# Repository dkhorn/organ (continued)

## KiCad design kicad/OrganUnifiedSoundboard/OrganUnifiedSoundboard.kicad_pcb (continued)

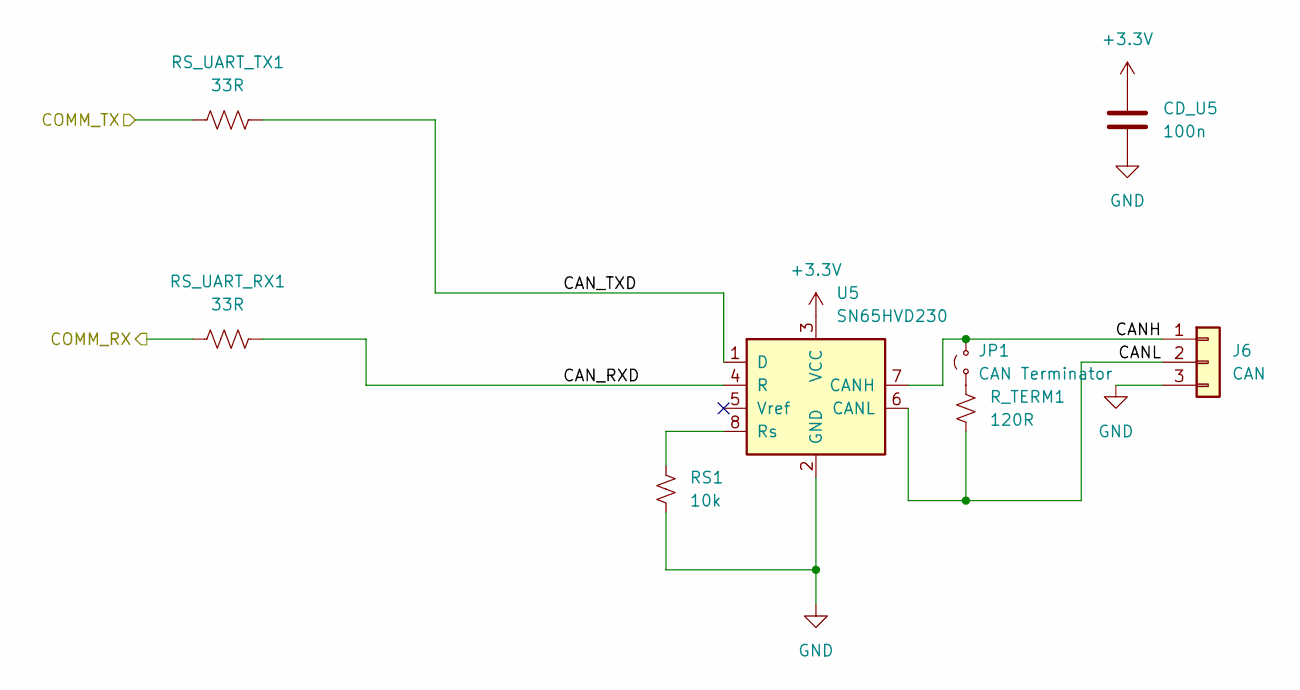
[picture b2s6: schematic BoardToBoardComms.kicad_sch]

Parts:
CD_U5: 100n; C_0603_1608Metric
J6: CAN; JST_PH_B3B-PH-K_1x03_P2.00mm_Vertical
JP1: CAN Terminator; PinHeader_1x02_P2.54mm_Vertical
RS1: 10k; R_0603_1608Metric
RS_UART_RX1: 33R; R_0603_1608Metric
RS_UART_TX1: 33R; R_0603_1608Metric
R_TERM1: 120R; R_0603_1608Metric
U5: SN65HVD230; SOIC-8_3.9x4.9mm_P1.27mm

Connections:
+3.3V: CD_U5.1, U5.3 (VCC); also elsewhere on the board
/Controller/BoardToBoardComms/CANH: J6.1, JP1.2 (B), U5.7 (CANH); also elsewhere on the board
/Controller/BoardToBoardComms/CANL: J6.2, R_TERM1.2, U5.6 (CANL); also elsewhere on the board
/Controller/BoardToBoardComms/CAN_RXD: RS_UART_RX1.2, U5.4 (R)
/Controller/BoardToBoardComms/CAN_TXD: RS_UART_TX1.2, U5.1 (D)
/Controller/COMM_RX: RS_UART_RX1.1; also elsewhere on the board
/Controller/COMM_TX: RS_UART_TX1.1; also elsewhere on the board
GND: CD_U5.2, J6.3, RS1.2, U5.2 (GND); also elsewhere on the board
unnamed: JP1.1 (A), R_TERM1.1
unnamed: RS1.1, U5.8 (Rs)

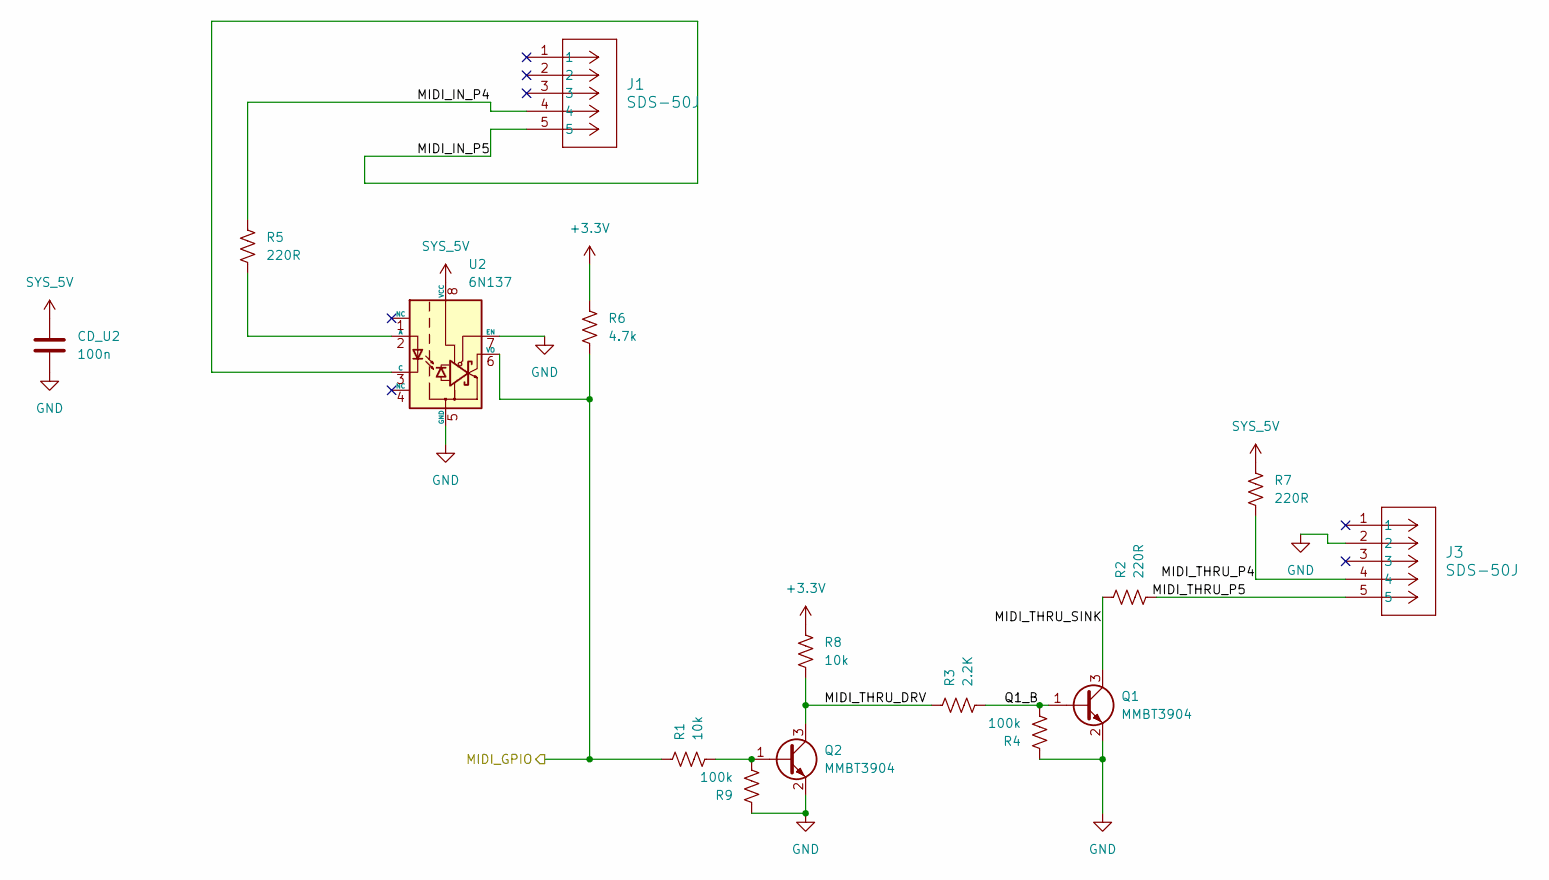
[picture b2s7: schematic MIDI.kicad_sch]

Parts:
CD_U2: 100n; C_0603_1608Metric
J1, J3: SDS-50J; CONN5_SDS-50J_CUD
Q1, Q2: MMBT3904; SOT-23
R1, R8: 10k; R_0603_1608Metric
R2, R5, R7: 220R; R_0603_1608Metric
R3: 2.2K; R_0603_1608Metric
R4, R9: 100k; R_0603_1608Metric
R6: 4.7k; R_0603_1608Metric
U2: 6N137; DIP-8_W7.62mm

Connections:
+3.3V: R6.1, R8.1; also elsewhere on the board
/Controller/MIDI/MIDI_IN_P4: J1.4, R5.1
/Controller/MIDI/MIDI_IN_P5: J1.5, U2.3 (C)
/Controller/MIDI/MIDI_THRU_DRV: Q2.3 (C), R3.1, R8.2
/Controller/MIDI/MIDI_THRU_P4: J3.4, R7.2
/Controller/MIDI/MIDI_THRU_P5: J3.5, R2.2
/Controller/MIDI/MIDI_THRU_SINK: Q1.3 (C), R2.1
/Controller/MIDI/Q1_B: Q1.1 (B), R3.2, R4.2
/Controller/MIDI_GPIO: R1.1, R6.2, U2.6 (VO); also elsewhere on the board
GND: CD_U2.2, J3.2, Q1.2 (E), Q2.2 (E), R4.1, R9.1, U2.5 (GND), U2.7 (EN); also elsewhere on the board
unnamed: Q2.1 (B), R1.2, R9.2
unnamed: R5.2, U2.2 (A)
SYS_5V: CD_U2.1, R7.1, U2.8 (VCC); also elsewhere on the board

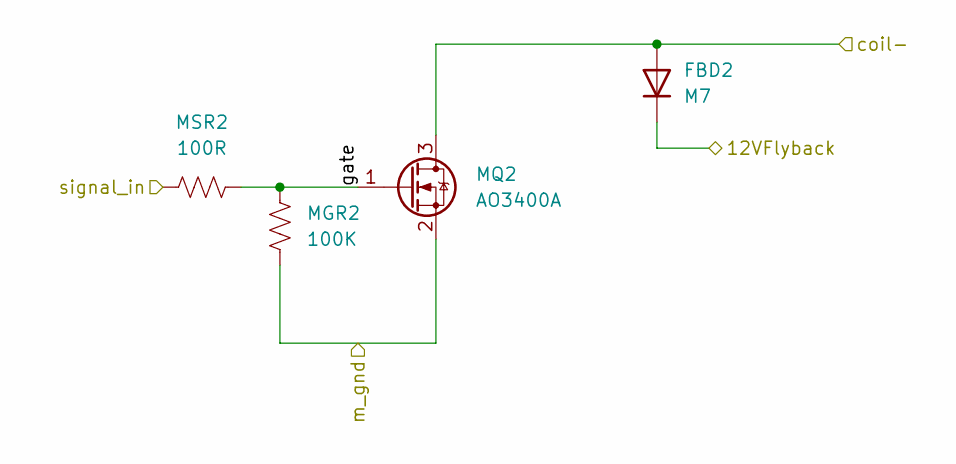
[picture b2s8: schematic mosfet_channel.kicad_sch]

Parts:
FBD2: M7; D_SMA
MGR2: 100K; R_0603_1608Metric
MQ2: AO3400A; SOT-23
MSR2: 100R; R_0603_1608Metric

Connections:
+12V: FBD2.1 (K); also elsewhere on the board
/outputs/16_channel_output_block/16_channel_mosfet_output/mosfet_channel1/gate: MGR2.1, MQ2.1 (G), MSR2.2
/outputs/16_channel_output_block/GND_COIL: MGR2.2, MQ2.2 (S); also elsewhere on the board
/outputs/16_channel_output_block/N01: MSR2.1; also elsewhere on the board
/outputs/coil_o1: FBD2.2 (A), MQ2.3 (D); also elsewhere on the board

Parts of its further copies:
FBD1, FBD3, FBD4, FBD5, FBD6, FBD7, FBD8, FBD9, FBD10, FBD11, FBD12, FBD13, FBD14, FBD15, FBD16, FBD17, FBD18, FBD19, FBD20, FBD21, FBD22, FBD23, FBD24, FBD25, FBD26, FBD27, FBD28, FBD29, FBD30, FBD31, FBD32, FBD33, FBD34, FBD35, FBD36, FBD37, FBD38, FBD39, FBD40, FBD41, FBD42, FBD43, FBD44, FBD45, FBD46, FBD47, FBD48, FBD49, FBD50, FBD51, FBD52, FBD53, FBD54, FBD55, FBD56, FBD57, FBD58, FBD59, FBD60, FBD61, FBD62, FBD63, FBD64, FBD65, FBD66, FBD67, FBD68, FBD69, FBD70, FBD71, FBD72, FBD73, FBD74, FBD75, FBD76, FBD77, FBD78, FBD79, FBD80: M7; D_SMA
MGR1, MGR3, MGR4, MGR5, MGR6, MGR7, MGR8, MGR9, MGR10, MGR11, MGR12, MGR13, MGR14, MGR15, MGR16, MGR17, MGR18, MGR19, MGR20, MGR21, MGR22, MGR23, MGR24, MGR25, MGR26, MGR27, MGR28, MGR29, MGR30, MGR31, MGR32, MGR33, MGR34, MGR35, MGR36, MGR37, MGR38, MGR39, MGR40, MGR41, MGR42, MGR43, MGR44, MGR45, MGR46, MGR47, MGR48, MGR49, MGR50, MGR51, MGR52, MGR53, MGR54, MGR55, MGR56, MGR57, MGR58, MGR59, MGR60, MGR61, MGR62, MGR63, MGR64, MGR65, MGR66, MGR67, MGR68, MGR69, MGR70, MGR71, MGR72, MGR73, MGR74, MGR75, MGR76, MGR77, MGR78, MGR79, MGR80: 100K; R_0603_1608Metric
MQ1, MQ3, MQ4, MQ5, MQ6, MQ7, MQ8, MQ9, MQ10, MQ11, MQ12, MQ13, MQ14, MQ15, MQ16, MQ17, MQ18, MQ19, MQ20, MQ21, MQ22, MQ23, MQ24, MQ25, MQ26, MQ27, MQ28, MQ29, MQ30, MQ31, MQ32, MQ33, MQ34, MQ35, MQ36, MQ37, MQ38, MQ39, MQ40, MQ41, MQ42, MQ43, MQ44, MQ45, MQ46, MQ47, MQ48, MQ49, MQ50, MQ51, MQ52, MQ53, MQ54, MQ55, MQ56, MQ57, MQ58, MQ59, MQ60, MQ61, MQ62, MQ63, MQ64, MQ65, MQ66, MQ67, MQ68, MQ69, MQ70, MQ71, MQ72, MQ73, MQ74, MQ75, MQ76, MQ77, MQ78, MQ79, MQ80: AO3400A; SOT-23
MSR1, MSR3, MSR4, MSR5, MSR6, MSR7, MSR8, MSR9, MSR10, MSR11, MSR12, MSR13, MSR14, MSR15, MSR16, MSR17, MSR18, MSR19, MSR20, MSR21, MSR22, MSR23, MSR24, MSR25, MSR26, MSR27, MSR28, MSR29, MSR30, MSR31, MSR32, MSR33, MSR34, MSR35, MSR36, MSR37, MSR38, MSR39, MSR40, MSR41, MSR42, MSR43, MSR44, MSR45, MSR46, MSR47, MSR48, MSR49, MSR50, MSR51, MSR52, MSR53, MSR54, MSR55, MSR56, MSR57, MSR58, MSR59, MSR60, MSR61, MSR62, MSR63, MSR64, MSR65, MSR66, MSR67, MSR68, MSR69, MSR70, MSR71, MSR72, MSR73, MSR74, MSR75, MSR76, MSR77, MSR78, MSR79, MSR80: 100R; R_0603_1608Metric

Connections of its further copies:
+12V: FBD1.1 (K), FBD3.1 (K), FBD4.1 (K), FBD5.1 (K), FBD6.1 (K), FBD7.1 (K), FBD8.1 (K), FBD9.1 (K), FBD10.1 (K), FBD11.1 (K), FBD12.1 (K), FBD13.1 (K), FBD14.1 (K), FBD15.1 (K), FBD16.1 (K), FBD17.1 (K), FBD18.1 (K), FBD19.1 (K), FBD20.1 (K), FBD21.1 (K), FBD22.1 (K), FBD23.1 (K), FBD24.1 (K), FBD25.1 (K), FBD26.1 (K), FBD27.1 (K), FBD28.1 (K), FBD29.1 (K), FBD30.1 (K), FBD31.1 (K), FBD32.1 (K), FBD33.1 (K), FBD34.1 (K), FBD35.1 (K), FBD36.1 (K), FBD37.1 (K), FBD38.1 (K), FBD39.1 (K), FBD40.1 (K), FBD41.1 (K), FBD42.1 (K), FBD43.1 (K), FBD44.1 (K), FBD45.1 (K), FBD46.1 (K), FBD47.1 (K), FBD48.1 (K), FBD49.1 (K), FBD50.1 (K), FBD51.1 (K), FBD52.1 (K), FBD53.1 (K), FBD54.1 (K), FBD55.1 (K), FBD56.1 (K), FBD57.1 (K), FBD58.1 (K), FBD59.1 (K), FBD60.1 (K), FBD61.1 (K), FBD62.1 (K), FBD63.1 (K), FBD64.1 (K), FBD65.1 (K), FBD66.1 (K), FBD67.1 (K), FBD68.1 (K), FBD69.1 (K), FBD70.1 (K), FBD71.1 (K), FBD72.1 (K), FBD73.1 (K), FBD74.1 (K), FBD75.1 (K), FBD76.1 (K), FBD77.1 (K), FBD78.1 (K), FBD79.1 (K), FBD80.1 (K); also elsewhere on the board
/outputs/16_channel_output_block1/16_channel_mosfet_output/mosfet_channel1/gate: MGR17.1, MQ17.1 (G), MSR17.2
/outputs/16_channel_output_block1/16_channel_mosfet_output/mosfet_channel2/gate: MGR18.1, MQ18.1 (G), MSR18.2
/outputs/16_channel_output_block1/16_channel_mosfet_output/mosfet_channel3/gate: MGR20.1, MQ20.1 (G), MSR20.2
/outputs/16_channel_output_block1/16_channel_mosfet_output/mosfet_channel4/gate: MGR19.1, MQ19.1 (G), MSR19.2
/outputs/16_channel_output_block1/16_channel_mosfet_output/mosfet_channel5/gate: MGR29.1, MQ29.1 (G), MSR29.2
/outputs/16_channel_output_block1/16_channel_mosfet_output/mosfet_channel6/gate: MGR30.1, MQ30.1 (G), MSR30.2
/outputs/16_channel_output_block1/16_channel_mosfet_output/mosfet_channel7/gate: MGR31.1, MQ31.1 (G), MSR31.2
/outputs/16_channel_output_block1/16_channel_mosfet_output/mosfet_channel8/gate: MGR32.1, MQ32.1 (G), MSR32.2
/outputs/16_channel_output_block1/16_channel_mosfet_output/mosfet_channel9/gate: MGR22.1, MQ22.1 (G), MSR22.2
/outputs/16_channel_output_block1/16_channel_mosfet_output/mosfet_channel10/gate: MGR21.1, MQ21.1 (G), MSR21.2
/outputs/16_channel_output_block1/16_channel_mosfet_output/mosfet_channel11/gate: MGR23.1, MQ23.1 (G), MSR23.2
/outputs/16_channel_output_block1/16_channel_mosfet_output/mosfet_channel12/gate: MGR24.1, MQ24.1 (G), MSR24.2
/outputs/16_channel_output_block1/16_channel_mosfet_output/mosfet_channel13/gate: MGR27.1, MQ27.1 (G), MSR27.2
/outputs/16_channel_output_block1/16_channel_mosfet_output/mosfet_channel14/gate: MGR26.1, MQ26.1 (G), MSR26.2
/outputs/16_channel_output_block1/16_channel_mosfet_output/mosfet_channel15/gate: MGR28.1, MQ28.1 (G), MSR28.2
/outputs/16_channel_output_block1/16_channel_mosfet_output/mosfet_channel16/gate: MGR25.1, MQ25.1 (G), MSR25.2
/outputs/16_channel_output_block1/GND_COIL: MGR17.2, MGR18.2, MGR19.2, MGR20.2, MGR21.2, MGR22.2, MGR23.2, MGR24.2, MGR25.2, MGR26.2, MGR27.2, MGR28.2, MGR29.2, MGR30.2, MGR31.2, MGR32.2, MQ17.2 (S), MQ18.2 (S), MQ19.2 (S), MQ20.2 (S), MQ21.2 (S), MQ22.2 (S), MQ23.2 (S), MQ24.2 (S), MQ25.2 (S), MQ26.2 (S), MQ27.2 (S), MQ28.2 (S), MQ29.2 (S), MQ30.2 (S), MQ31.2 (S), MQ32.2 (S); also elsewhere on the board
/outputs/16_channel_output_block1/N01: MSR17.1; also elsewhere on the board
/outputs/16_channel_output_block1/N02: MSR18.1; also elsewhere on the board
/outputs/16_channel_output_block1/N03: MSR20.1; also elsewhere on the board
/outputs/16_channel_output_block1/N04: MSR19.1; also elsewhere on the board
/outputs/16_channel_output_block1/N05: MSR29.1; also elsewhere on the board
/outputs/16_channel_output_block1/N06: MSR30.1; also elsewhere on the board
/outputs/16_channel_output_block1/N07: MSR31.1; also elsewhere on the board
/outputs/16_channel_output_block1/N08: MSR32.1; also elsewhere on the board
/outputs/16_channel_output_block1/N09: MSR22.1; also elsewhere on the board
/outputs/16_channel_output_block1/N10: MSR21.1; also elsewhere on the board
/outputs/16_channel_output_block1/N11: MSR23.1; also elsewhere on the board
/outputs/16_channel_output_block1/N12: MSR24.1; also elsewhere on the board
/outputs/16_channel_output_block1/N13: MSR27.1; also elsewhere on the board
/outputs/16_channel_output_block1/N14: MSR26.1; also elsewhere on the board
/outputs/16_channel_output_block1/N15: MSR28.1; also elsewhere on the board
/outputs/16_channel_output_block1/N16: MSR25.1; also elsewhere on the board
/outputs/16_channel_output_block2/16_channel_mosfet_output/mosfet_channel1/gate: MGR33.1, MQ33.1 (G), MSR33.2
/outputs/16_channel_output_block2/16_channel_mosfet_output/mosfet_channel2/gate: MGR34.1, MQ34.1 (G), MSR34.2
/outputs/16_channel_output_block2/16_channel_mosfet_output/mosfet_channel3/gate: MGR36.1, MQ36.1 (G), MSR36.2
/outputs/16_channel_output_block2/16_channel_mosfet_output/mosfet_channel4/gate: MGR35.1, MQ35.1 (G), MSR35.2
/outputs/16_channel_output_block2/16_channel_mosfet_output/mosfet_channel5/gate: MGR45.1, MQ45.1 (G), MSR45.2
/outputs/16_channel_output_block2/16_channel_mosfet_output/mosfet_channel6/gate: MGR46.1, MQ46.1 (G), MSR46.2
/outputs/16_channel_output_block2/16_channel_mosfet_output/mosfet_channel7/gate: MGR47.1, MQ47.1 (G), MSR47.2
/outputs/16_channel_output_block2/16_channel_mosfet_output/mosfet_channel8/gate: MGR48.1, MQ48.1 (G), MSR48.2
/outputs/16_channel_output_block2/16_channel_mosfet_output/mosfet_channel9/gate: MGR38.1, MQ38.1 (G), MSR38.2
/outputs/16_channel_output_block2/16_channel_mosfet_output/mosfet_channel10/gate: MGR37.1, MQ37.1 (G), MSR37.2
/outputs/16_channel_output_block2/16_channel_mosfet_output/mosfet_channel11/gate: MGR39.1, MQ39.1 (G), MSR39.2
/outputs/16_channel_output_block2/16_channel_mosfet_output/mosfet_channel12/gate: MGR40.1, MQ40.1 (G), MSR40.2
/outputs/16_channel_output_block2/16_channel_mosfet_output/mosfet_channel13/gate: MGR43.1, MQ43.1 (G), MSR43.2
/outputs/16_channel_output_block2/16_channel_mosfet_output/mosfet_channel14/gate: MGR42.1, MQ42.1 (G), MSR42.2
/outputs/16_channel_output_block2/16_channel_mosfet_output/mosfet_channel15/gate: MGR44.1, MQ44.1 (G), MSR44.2
/outputs/16_channel_output_block2/16_channel_mosfet_output/mosfet_channel16/gate: MGR41.1, MQ41.1 (G), MSR41.2
/outputs/16_channel_output_block2/GND_COIL: MGR33.2, MGR34.2, MGR35.2, MGR36.2, MGR37.2, MGR38.2, MGR39.2, MGR40.2, MGR41.2, MGR42.2, MGR43.2, MGR44.2, MGR45.2, MGR46.2, MGR47.2, MGR48.2, MQ33.2 (S), MQ34.2 (S), MQ35.2 (S), MQ36.2 (S), MQ37.2 (S), MQ38.2 (S), MQ39.2 (S), MQ40.2 (S), MQ41.2 (S), MQ42.2 (S), MQ43.2 (S), MQ44.2 (S), MQ45.2 (S), MQ46.2 (S), MQ47.2 (S), MQ48.2 (S); also elsewhere on the board
/outputs/16_channel_output_block2/N01: MSR33.1; also elsewhere on the board
/outputs/16_channel_output_block2/N02: MSR34.1; also elsewhere on the board
/outputs/16_channel_output_block2/N03: MSR36.1; also elsewhere on the board
/outputs/16_channel_output_block2/N04: MSR35.1; also elsewhere on the board
/outputs/16_channel_output_block2/N05: MSR45.1; also elsewhere on the board
/outputs/16_channel_output_block2/N06: MSR46.1; also elsewhere on the board
/outputs/16_channel_output_block2/N07: MSR47.1; also elsewhere on the board
/outputs/16_channel_output_block2/N08: MSR48.1; also elsewhere on the board
/outputs/16_channel_output_block2/N09: MSR38.1; also elsewhere on the board
/outputs/16_channel_output_block2/N10: MSR37.1; also elsewhere on the board
/outputs/16_channel_output_block2/N11: MSR39.1; also elsewhere on the board
/outputs/16_channel_output_block2/N12: MSR40.1; also elsewhere on the board
/outputs/16_channel_output_block2/N13: MSR43.1; also elsewhere on the board
/outputs/16_channel_output_block2/N14: MSR42.1; also elsewhere on the board
/outputs/16_channel_output_block2/N15: MSR44.1; also elsewhere on the board
/outputs/16_channel_output_block2/N16: MSR41.1; also elsewhere on the board
/outputs/16_channel_output_block3/16_channel_mosfet_output/mosfet_channel1/gate: MGR49.1, MQ49.1 (G), MSR49.2
/outputs/16_channel_output_block3/16_channel_mosfet_output/mosfet_channel2/gate: MGR50.1, MQ50.1 (G), MSR50.2
/outputs/16_channel_output_block3/16_channel_mosfet_output/mosfet_channel3/gate: MGR52.1, MQ52.1 (G), MSR52.2
/outputs/16_channel_output_block3/16_channel_mosfet_output/mosfet_channel4/gate: MGR51.1, MQ51.1 (G), MSR51.2
/outputs/16_channel_output_block3/16_channel_mosfet_output/mosfet_channel5/gate: MGR61.1, MQ61.1 (G), MSR61.2
/outputs/16_channel_output_block3/16_channel_mosfet_output/mosfet_channel6/gate: MGR62.1, MQ62.1 (G), MSR62.2
/outputs/16_channel_output_block3/16_channel_mosfet_output/mosfet_channel7/gate: MGR63.1, MQ63.1 (G), MSR63.2
/outputs/16_channel_output_block3/16_channel_mosfet_output/mosfet_channel8/gate: MGR64.1, MQ64.1 (G), MSR64.2
/outputs/16_channel_output_block3/16_channel_mosfet_output/mosfet_channel9/gate: MGR54.1, MQ54.1 (G), MSR54.2
/outputs/16_channel_output_block3/16_channel_mosfet_output/mosfet_channel10/gate: MGR53.1, MQ53.1 (G), MSR53.2
/outputs/16_channel_output_block3/16_channel_mosfet_output/mosfet_channel11/gate: MGR55.1, MQ55.1 (G), MSR55.2
/outputs/16_channel_output_block3/16_channel_mosfet_output/mosfet_channel12/gate: MGR56.1, MQ56.1 (G), MSR56.2
/outputs/16_channel_output_block3/16_channel_mosfet_output/mosfet_channel13/gate: MGR59.1, MQ59.1 (G), MSR59.2
/outputs/16_channel_output_block3/16_channel_mosfet_output/mosfet_channel14/gate: MGR58.1, MQ58.1 (G), MSR58.2
/outputs/16_channel_output_block3/16_channel_mosfet_output/mosfet_channel15/gate: MGR60.1, MQ60.1 (G), MSR60.2
/outputs/16_channel_output_block3/16_channel_mosfet_output/mosfet_channel16/gate: MGR57.1, MQ57.1 (G), MSR57.2
/outputs/16_channel_output_block3/GND_COIL: MGR49.2, MGR50.2, MGR51.2, MGR52.2, MGR53.2, MGR54.2, MGR55.2, MGR56.2, MGR57.2, MGR58.2, MGR59.2, MGR60.2, MGR61.2, MGR62.2, MGR63.2, MGR64.2, MQ49.2 (S), MQ50.2 (S), MQ51.2 (S), MQ52.2 (S), MQ53.2 (S), MQ54.2 (S), MQ55.2 (S), MQ56.2 (S), MQ57.2 (S), MQ58.2 (S), MQ59.2 (S), MQ60.2 (S), MQ61.2 (S), MQ62.2 (S), MQ63.2 (S), MQ64.2 (S); also elsewhere on the board
/outputs/16_channel_output_block3/N01: MSR49.1; also elsewhere on the board
/outputs/16_channel_output_block3/N02: MSR50.1; also elsewhere on the board
/outputs/16_channel_output_block3/N03: MSR52.1; also elsewhere on the board
/outputs/16_channel_output_block3/N04: MSR51.1; also elsewhere on the board
/outputs/16_channel_output_block3/N05: MSR61.1; also elsewhere on the board
/outputs/16_channel_output_block3/N06: MSR62.1; also elsewhere on the board
/outputs/16_channel_output_block3/N07: MSR63.1; also elsewhere on the board
/outputs/16_channel_output_block3/N08: MSR64.1; also elsewhere on the board
/outputs/16_channel_output_block3/N09: MSR54.1; also elsewhere on the board
/outputs/16_channel_output_block3/N10: MSR53.1; also elsewhere on the board
/outputs/16_channel_output_block3/N11: MSR55.1; also elsewhere on the board
/outputs/16_channel_output_block3/N12: MSR56.1; also elsewhere on the board
/outputs/16_channel_output_block3/N13: MSR59.1; also elsewhere on the board
/outputs/16_channel_output_block3/N14: MSR58.1; also elsewhere on the board
/outputs/16_channel_output_block3/N15: MSR60.1; also elsewhere on the board
/outputs/16_channel_output_block3/N16: MSR57.1; also elsewhere on the board
/outputs/16_channel_output_block4/16_channel_mosfet_output/mosfet_channel1/gate: MGR65.1, MQ65.1 (G), MSR65.2
/outputs/16_channel_output_block4/16_channel_mosfet_output/mosfet_channel2/gate: MGR66.1, MQ66.1 (G), MSR66.2
/outputs/16_channel_output_block4/16_channel_mosfet_output/mosfet_channel3/gate: MGR68.1, MQ68.1 (G), MSR68.2
/outputs/16_channel_output_block4/16_channel_mosfet_output/mosfet_channel4/gate: MGR67.1, MQ67.1 (G), MSR67.2
/outputs/16_channel_output_block4/16_channel_mosfet_output/mosfet_channel5/gate: MGR77.1, MQ77.1 (G), MSR77.2
/outputs/16_channel_output_block4/16_channel_mosfet_output/mosfet_channel6/gate: MGR78.1, MQ78.1 (G), MSR78.2
/outputs/16_channel_output_block4/16_channel_mosfet_output/mosfet_channel7/gate: MGR79.1, MQ79.1 (G), MSR79.2
/outputs/16_channel_output_block4/16_channel_mosfet_output/mosfet_channel8/gate: MGR80.1, MQ80.1 (G), MSR80.2
/outputs/16_channel_output_block4/16_channel_mosfet_output/mosfet_channel9/gate: MGR70.1, MQ70.1 (G), MSR70.2
/outputs/16_channel_output_block4/16_channel_mosfet_output/mosfet_channel10/gate: MGR69.1, MQ69.1 (G), MSR69.2
/outputs/16_channel_output_block4/16_channel_mosfet_output/mosfet_channel11/gate: MGR71.1, MQ71.1 (G), MSR71.2
/outputs/16_channel_output_block4/16_channel_mosfet_output/mosfet_channel12/gate: MGR72.1, MQ72.1 (G), MSR72.2
/outputs/16_channel_output_block4/16_channel_mosfet_output/mosfet_channel13/gate: MGR75.1, MQ75.1 (G), MSR75.2
/outputs/16_channel_output_block4/16_channel_mosfet_output/mosfet_channel14/gate: MGR74.1, MQ74.1 (G), MSR74.2
/outputs/16_channel_output_block4/16_channel_mosfet_output/mosfet_channel15/gate: MGR76.1, MQ76.1 (G), MSR76.2
/outputs/16_channel_output_block4/16_channel_mosfet_output/mosfet_channel16/gate: MGR73.1, MQ73.1 (G), MSR73.2
/outputs/16_channel_output_block4/GND_COIL: MGR65.2, MGR66.2, MGR67.2, MGR68.2, MGR69.2, MGR70.2, MGR71.2, MGR72.2, MGR73.2, MGR74.2, MGR75.2, MGR76.2, MGR77.2, MGR78.2, MGR79.2, MGR80.2, MQ65.2 (S), MQ66.2 (S), MQ67.2 (S), MQ68.2 (S), MQ69.2 (S), MQ70.2 (S), MQ71.2 (S), MQ72.2 (S), MQ73.2 (S), MQ74.2 (S), MQ75.2 (S), MQ76.2 (S), MQ77.2 (S), MQ78.2 (S), MQ79.2 (S), MQ80.2 (S); also elsewhere on the board
/outputs/16_channel_output_block4/N01: MSR65.1; also elsewhere on the board
/outputs/16_channel_output_block4/N02: MSR66.1; also elsewhere on the board
/outputs/16_channel_output_block4/N03: MSR68.1; also elsewhere on the board
/outputs/16_channel_output_block4/N04: MSR67.1; also elsewhere on the board
/outputs/16_channel_output_block4/N05: MSR77.1; also elsewhere on the board
/outputs/16_channel_output_block4/N06: MSR78.1; also elsewhere on the board
/outputs/16_channel_output_block4/N07: MSR79.1; also elsewhere on the board
/outputs/16_channel_output_block4/N08: MSR80.1; also elsewhere on the board
/outputs/16_channel_output_block4/N09: MSR70.1; also elsewhere on the board
/outputs/16_channel_output_block4/N10: MSR69.1; also elsewhere on the board
/outputs/16_channel_output_block4/N11: MSR71.1; also elsewhere on the board
/outputs/16_channel_output_block4/N12: MSR72.1; also elsewhere on the board
/outputs/16_channel_output_block4/N13: MSR75.1; also elsewhere on the board
/outputs/16_channel_output_block4/N14: MSR74.1; also elsewhere on the board
/outputs/16_channel_output_block4/N15: MSR76.1; also elsewhere on the board
/outputs/16_channel_output_block4/N16: MSR73.1; also elsewhere on the board
/outputs/16_channel_output_block/16_channel_mosfet_output/mosfet_channel2/gate: MGR3.1, MQ3.1 (G), MSR3.2
/outputs/16_channel_output_block/16_channel_mosfet_output/mosfet_channel3/gate: MGR4.1, MQ4.1 (G), MSR4.2
/outputs/16_channel_output_block/16_channel_mosfet_output/mosfet_channel4/gate: MGR5.1, MQ5.1 (G), MSR5.2
/outputs/16_channel_output_block/16_channel_mosfet_output/mosfet_channel5/gate: MGR6.1, MQ6.1 (G), MSR6.2
/outputs/16_channel_output_block/16_channel_mosfet_output/mosfet_channel6/gate: MGR7.1, MQ7.1 (G), MSR7.2
/outputs/16_channel_output_block/16_channel_mosfet_output/mosfet_channel7/gate: MGR8.1, MQ8.1 (G), MSR8.2
/outputs/16_channel_output_block/16_channel_mosfet_output/mosfet_channel8/gate: MGR9.1, MQ9.1 (G), MSR9.2
/outputs/16_channel_output_block/16_channel_mosfet_output/mosfet_channel9/gate: MGR10.1, MQ10.1 (G), MSR10.2
/outputs/16_channel_output_block/16_channel_mosfet_output/mosfet_channel10/gate: MGR11.1, MQ11.1 (G), MSR11.2
/outputs/16_channel_output_block/16_channel_mosfet_output/mosfet_channel11/gate: MGR12.1, MQ12.1 (G), MSR12.2
/outputs/16_channel_output_block/16_channel_mosfet_output/mosfet_channel12/gate: MGR13.1, MQ13.1 (G), MSR13.2
/outputs/16_channel_output_block/16_channel_mosfet_output/mosfet_channel13/gate: MGR14.1, MQ14.1 (G), MSR14.2
/outputs/16_channel_output_block/16_channel_mosfet_output/mosfet_channel14/gate: MGR15.1, MQ15.1 (G), MSR15.2
/outputs/16_channel_output_block/16_channel_mosfet_output/mosfet_channel15/gate: MGR16.1, MQ16.1 (G), MSR16.2
/outputs/16_channel_output_block/16_channel_mosfet_output/mosfet_channel16/gate: MGR1.1, MQ1.1 (G), MSR1.2
/outputs/16_channel_output_block/GND_COIL: MGR1.2, MGR3.2, MGR4.2, MGR5.2, MGR6.2, MGR7.2, MGR8.2, MGR9.2, MGR10.2, MGR11.2, MGR12.2, MGR13.2, MGR14.2, MGR15.2, MGR16.2, MQ1.2 (S), MQ3.2 (S), MQ4.2 (S), MQ5.2 (S), MQ6.2 (S), MQ7.2 (S), MQ8.2 (S), MQ9.2 (S), MQ10.2 (S), MQ11.2 (S), MQ12.2 (S), MQ13.2 (S), MQ14.2 (S), MQ15.2 (S), MQ16.2 (S); also elsewhere on the board
/outputs/16_channel_output_block/N02: MSR3.1; also elsewhere on the board
/outputs/16_channel_output_block/N03: MSR4.1; also elsewhere on the board
/outputs/16_channel_output_block/N04: MSR5.1; also elsewhere on the board
/outputs/16_channel_output_block/N05: MSR6.1; also elsewhere on the board
/outputs/16_channel_output_block/N06: MSR7.1; also elsewhere on the board
/outputs/16_channel_output_block/N07: MSR8.1; also elsewhere on the board
/outputs/16_channel_output_block/N08: MSR9.1; also elsewhere on the board
/outputs/16_channel_output_block/N09: MSR10.1; also elsewhere on the board
/outputs/16_channel_output_block/N10: MSR11.1; also elsewhere on the board
/outputs/16_channel_output_block/N11: MSR12.1; also elsewhere on the board
/outputs/16_channel_output_block/N12: MSR13.1; also elsewhere on the board
/outputs/16_channel_output_block/N13: MSR14.1; also elsewhere on the board
/outputs/16_channel_output_block/N14: MSR15.1; also elsewhere on the board
/outputs/16_channel_output_block/N15: MSR16.1; also elsewhere on the board
/outputs/16_channel_output_block/N16: MSR1.1; also elsewhere on the board
/outputs/coil_o2: FBD3.2 (A), MQ3.3 (D); also elsewhere on the board
/outputs/coil_o3: FBD4.2 (A), MQ4.3 (D); also elsewhere on the board
/outputs/coil_o4: FBD5.2 (A), MQ5.3 (D); also elsewhere on the board
/outputs/coil_o5: FBD6.2 (A), MQ6.3 (D); also elsewhere on the board
/outputs/coil_o6: FBD7.2 (A), MQ7.3 (D); also elsewhere on the board
/outputs/coil_o7: FBD8.2 (A), MQ8.3 (D); also elsewhere on the board
/outputs/coil_o8: FBD9.2 (A), MQ9.3 (D); also elsewhere on the board
/outputs/coil_o9: FBD10.2 (A), MQ10.3 (D); also elsewhere on the board
/outputs/coil_o10: FBD11.2 (A), MQ11.3 (D); also elsewhere on the board
/outputs/coil_o11: FBD12.2 (A), MQ12.3 (D); also elsewhere on the board
/outputs/coil_o12: FBD13.2 (A), MQ13.3 (D); also elsewhere on the board
/outputs/coil_o13: FBD14.2 (A), MQ14.3 (D); also elsewhere on the board
/outputs/coil_o14: FBD15.2 (A), MQ15.3 (D); also elsewhere on the board
/outputs/coil_o15: FBD16.2 (A), MQ16.3 (D); also elsewhere on the board
/outputs/coil_o16: FBD1.2 (A), MQ1.3 (D); also elsewhere on the board
/outputs/coil_o17: FBD17.2 (A), MQ17.3 (D); also elsewhere on the board
/outputs/coil_o18: FBD18.2 (A), MQ18.3 (D); also elsewhere on the board
/outputs/coil_o19: FBD20.2 (A), MQ20.3 (D); also elsewhere on the board
/outputs/coil_o20: FBD19.2 (A), MQ19.3 (D); also elsewhere on the board
/outputs/coil_o21: FBD29.2 (A), MQ29.3 (D); also elsewhere on the board
/outputs/coil_o22: FBD30.2 (A), MQ30.3 (D); also elsewhere on the board
/outputs/coil_o23: FBD31.2 (A), MQ31.3 (D); also elsewhere on the board
/outputs/coil_o24: FBD32.2 (A), MQ32.3 (D); also elsewhere on the board
/outputs/coil_o25: FBD22.2 (A), MQ22.3 (D); also elsewhere on the board
/outputs/coil_o26: FBD21.2 (A), MQ21.3 (D); also elsewhere on the board
/outputs/coil_o27: FBD23.2 (A), MQ23.3 (D); also elsewhere on the board
/outputs/coil_o28: FBD24.2 (A), MQ24.3 (D); also elsewhere on the board
/outputs/coil_o29: FBD27.2 (A), MQ27.3 (D); also elsewhere on the board
/outputs/coil_o30: FBD26.2 (A), MQ26.3 (D); also elsewhere on the board
/outputs/coil_o31: FBD28.2 (A), MQ28.3 (D); also elsewhere on the board
/outputs/coil_o32: FBD25.2 (A), MQ25.3 (D); also elsewhere on the board
/outputs/coil_o33: FBD33.2 (A), MQ33.3 (D); also elsewhere on the board
/outputs/coil_o34: FBD34.2 (A), MQ34.3 (D); also elsewhere on the board
/outputs/coil_o35: FBD36.2 (A), MQ36.3 (D); also elsewhere on the board
/outputs/coil_o36: FBD35.2 (A), MQ35.3 (D); also elsewhere on the board
/outputs/coil_o37: FBD45.2 (A), MQ45.3 (D); also elsewhere on the board
/outputs/coil_o38: FBD46.2 (A), MQ46.3 (D); also elsewhere on the board
/outputs/coil_o39: FBD47.2 (A), MQ47.3 (D); also elsewhere on the board
/outputs/coil_o40: FBD48.2 (A), MQ48.3 (D); also elsewhere on the board
/outputs/coil_o41: FBD38.2 (A), MQ38.3 (D); also elsewhere on the board
/outputs/coil_o42: FBD37.2 (A), MQ37.3 (D); also elsewhere on the board
/outputs/coil_o43: FBD39.2 (A), MQ39.3 (D); also elsewhere on the board
/outputs/coil_o44: FBD40.2 (A), MQ40.3 (D); also elsewhere on the board
/outputs/coil_o45: FBD43.2 (A), MQ43.3 (D); also elsewhere on the board
/outputs/coil_o46: FBD42.2 (A), MQ42.3 (D); also elsewhere on the board
/outputs/coil_o47: FBD44.2 (A), MQ44.3 (D); also elsewhere on the board
/outputs/coil_o48: FBD41.2 (A), MQ41.3 (D); also elsewhere on the board
/outputs/coil_o49: FBD49.2 (A), MQ49.3 (D); also elsewhere on the board
/outputs/coil_o50: FBD50.2 (A), MQ50.3 (D); also elsewhere on the board
/outputs/coil_o51: FBD52.2 (A), MQ52.3 (D); also elsewhere on the board
/outputs/coil_o52: FBD51.2 (A), MQ51.3 (D); also elsewhere on the board
/outputs/coil_o53: FBD61.2 (A), MQ61.3 (D); also elsewhere on the board
/outputs/coil_o54: FBD62.2 (A), MQ62.3 (D); also elsewhere on the board
/outputs/coil_o55: FBD63.2 (A), MQ63.3 (D); also elsewhere on the board
/outputs/coil_o56: FBD64.2 (A), MQ64.3 (D); also elsewhere on the board
/outputs/coil_o57: FBD54.2 (A), MQ54.3 (D); also elsewhere on the board
/outputs/coil_o58: FBD53.2 (A), MQ53.3 (D); also elsewhere on the board
/outputs/coil_o59: FBD55.2 (A), MQ55.3 (D); also elsewhere on the board
/outputs/coil_o60: FBD56.2 (A), MQ56.3 (D); also elsewhere on the board
/outputs/coil_o61: FBD59.2 (A), MQ59.3 (D); also elsewhere on the board
/outputs/coil_o62: FBD58.2 (A), MQ58.3 (D); also elsewhere on the board
/outputs/coil_o63: FBD60.2 (A), MQ60.3 (D); also elsewhere on the board
/outputs/coil_o64: FBD57.2 (A), MQ57.3 (D); also elsewhere on the board
/outputs/coil_o65: FBD65.2 (A), MQ65.3 (D); also elsewhere on the board
/outputs/coil_o66: FBD66.2 (A), MQ66.3 (D); also elsewhere on the board
/outputs/coil_o67: FBD68.2 (A), MQ68.3 (D); also elsewhere on the board
/outputs/coil_o68: FBD67.2 (A), MQ67.3 (D); also elsewhere on the board
/outputs/coil_o69: FBD77.2 (A), MQ77.3 (D); also elsewhere on the board
/outputs/coil_o70: FBD78.2 (A), MQ78.3 (D); also elsewhere on the board
/outputs/coil_o71: FBD79.2 (A), MQ79.3 (D); also elsewhere on the board
/outputs/coil_o72: FBD80.2 (A), MQ80.3 (D); also elsewhere on the board
/outputs/coil_o73: FBD70.2 (A), MQ70.3 (D); also elsewhere on the board
/outputs/coil_o74: FBD69.2 (A), MQ69.3 (D); also elsewhere on the board
/outputs/coil_o75: FBD71.2 (A), MQ71.3 (D); also elsewhere on the board
/outputs/coil_o76: FBD72.2 (A), MQ72.3 (D); also elsewhere on the board
/outputs/coil_o77: FBD75.2 (A), MQ75.3 (D); also elsewhere on the board
/outputs/coil_o78: FBD74.2 (A), MQ74.3 (D); also elsewhere on the board
/outputs/coil_o79: FBD76.2 (A), MQ76.3 (D); also elsewhere on the board
/outputs/coil_o80: FBD73.2 (A), MQ73.3 (D); also elsewhere on the board
